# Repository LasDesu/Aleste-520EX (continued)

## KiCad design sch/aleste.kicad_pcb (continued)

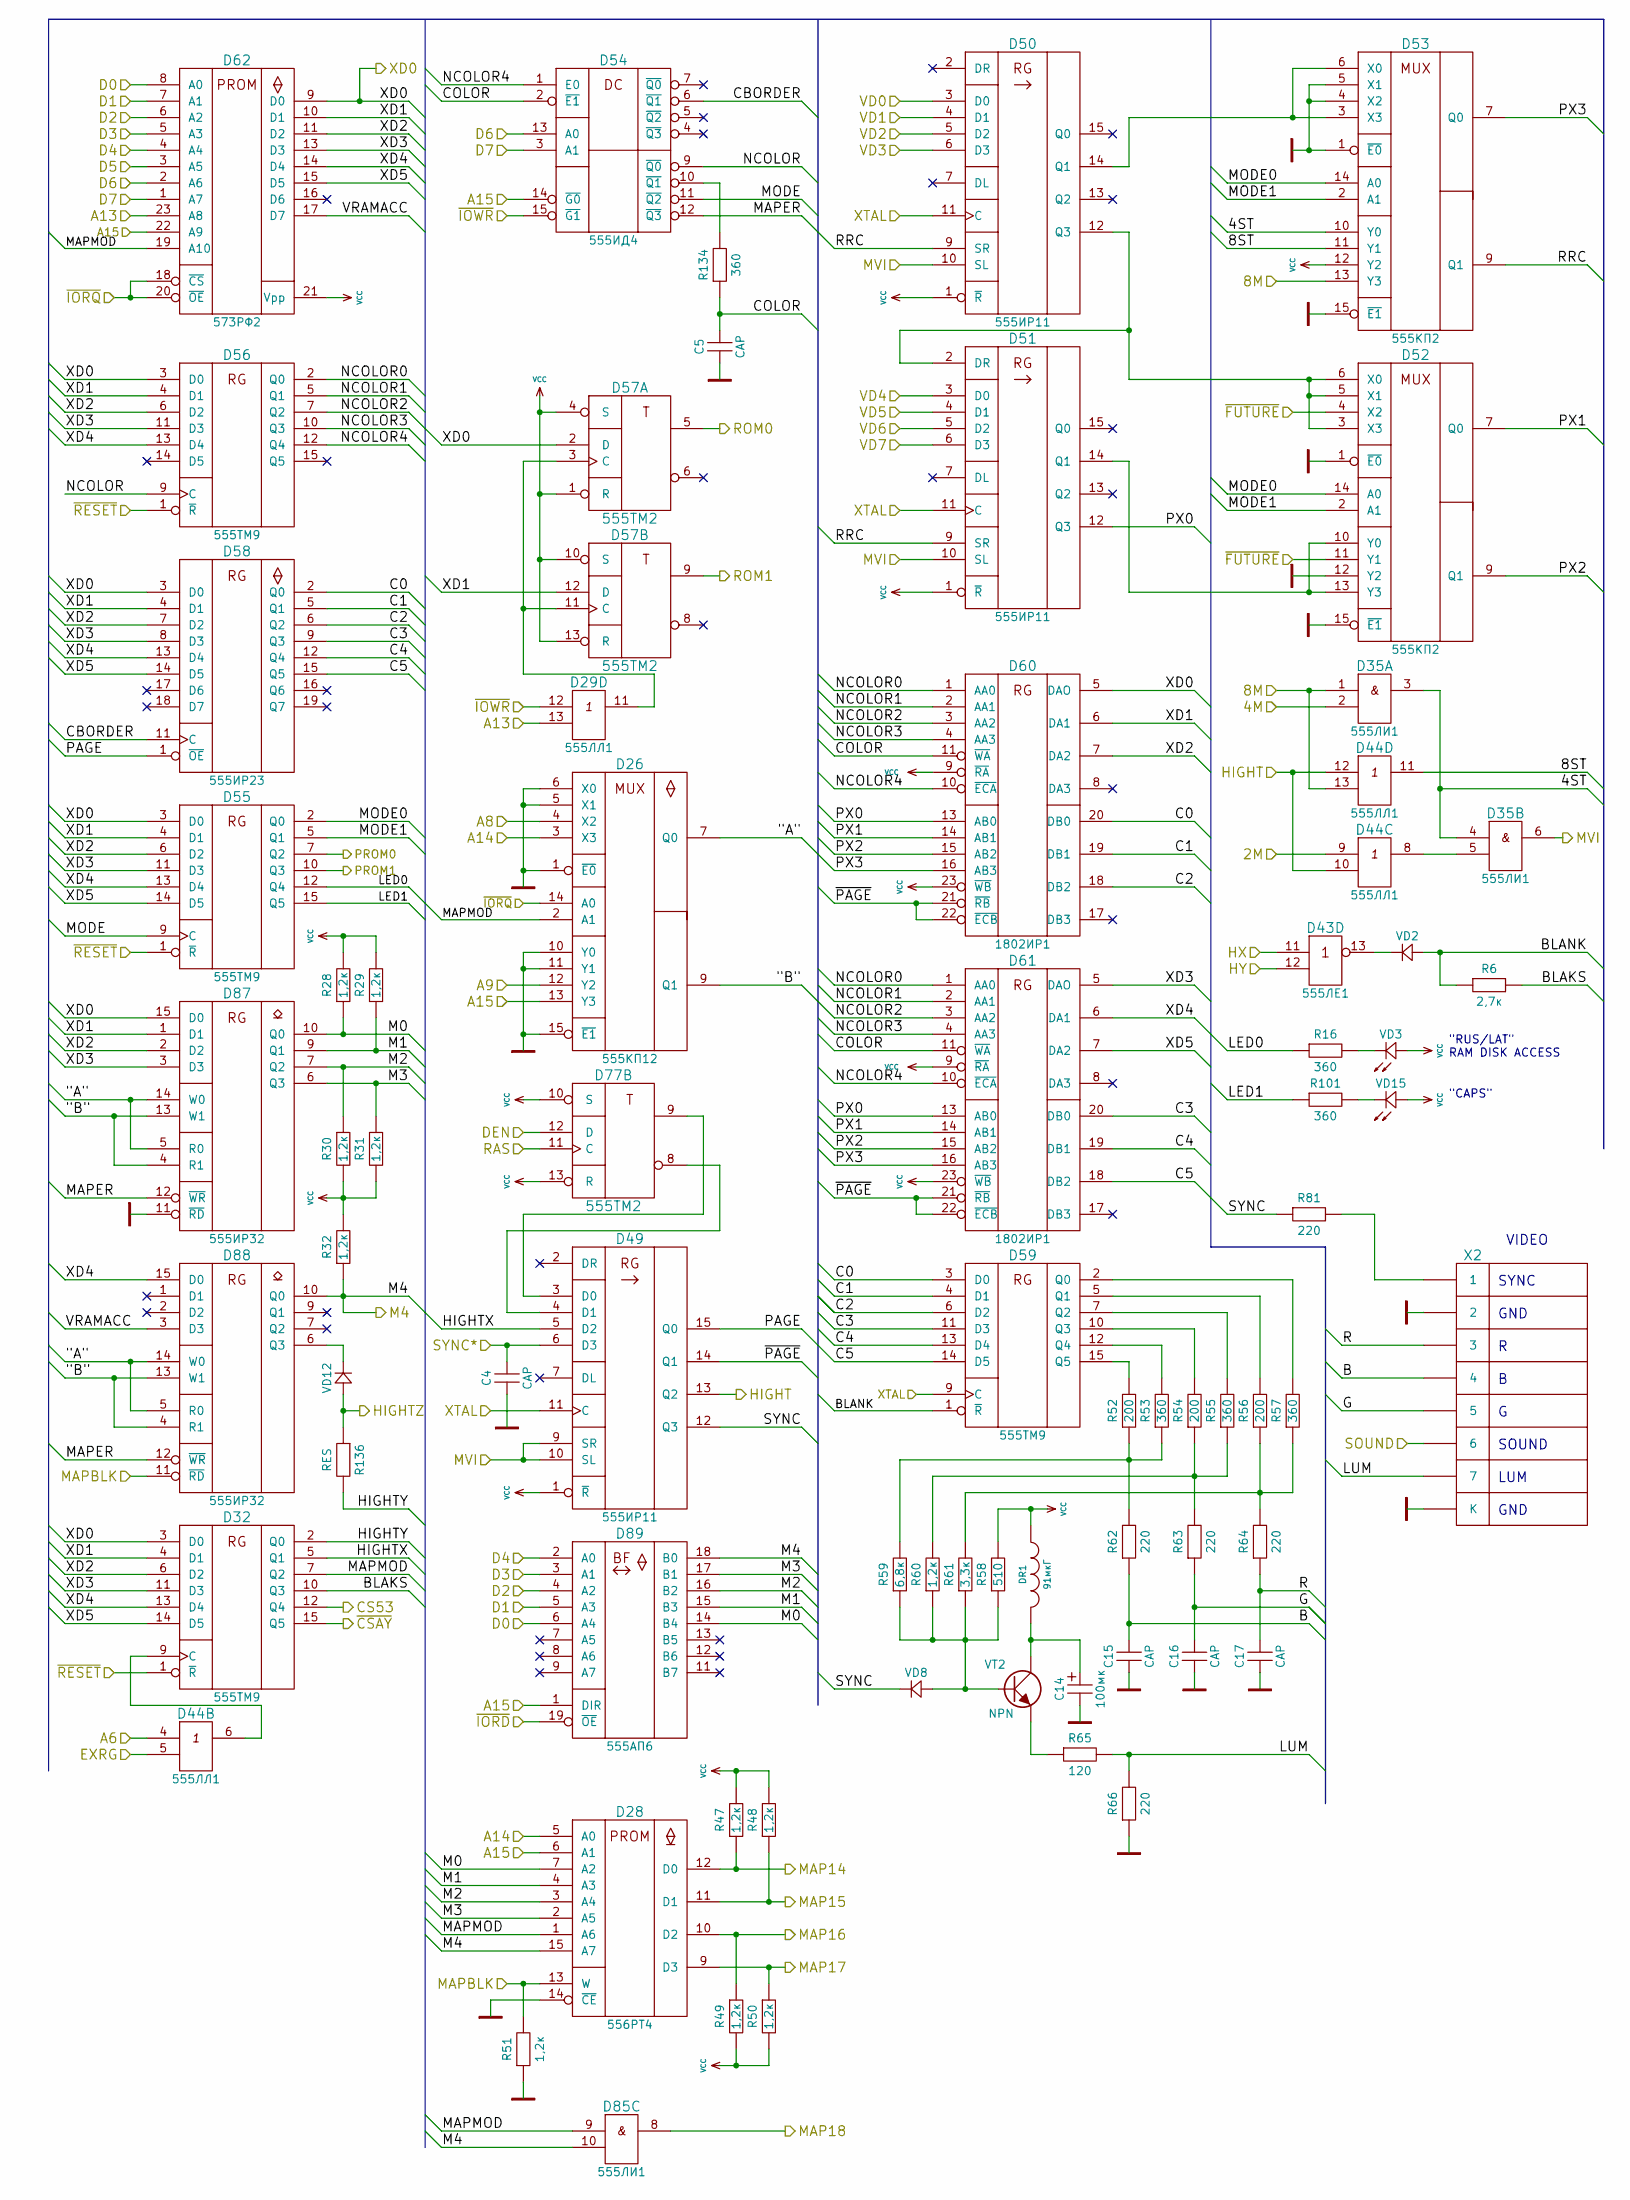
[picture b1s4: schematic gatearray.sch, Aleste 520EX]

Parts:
C4, C5, C15, C16, C17: CAP; C_Disc_D7.5_P2.5
C14: 100мк; C_Radial_D5_L6_P2.5
D26: 555КП12; DIP-16
D28: 556РТ4; DIP-16
D29, D44: 555ЛЛ1; DIP-14
D32, D55, D56, D59: 555ТМ9; DIP-16
D35, D85: 555ЛИ1; DIP-14
D43: 555ЛЕ1; DIP-14
D49, D50, D51: 555ИР11; DIP-16
D52, D53: 555КП2; DIP-16
D54: 555ИД4; DIP-16
D57, D77: 555ТМ2; DIP-14
D58: 555ИР23; DIP-20
D60, D61: 1802ИР1; DIP-24
D62: 573РФ2; DIP-24
D87, D88: 555ИР32; DIP-16
D89: 555АП6; DIP-20
DR1: 91мкГ; Choke_Horizontal_RM15mm
R6: 2,7к; Resistor_Horizontal_RM7.5mm
R16, R53, R55, R57, R101, R134: 360; Resistor_Horizontal_RM7.5mm
R28, R29, R30, R31, R32, R47, R48, R49, R50: 1,2к; Resistor_Vertical_RM2.5mm
R51, R60: 1,2к; Resistor_Horizontal_RM7.5mm
R52, R54, R56: 200; Resistor_Horizontal_RM7.5mm
R58: 510; Resistor_Horizontal_RM7.5mm
R59: 6,8к; Resistor_Horizontal_RM7.5mm
R61: 3,3к; Resistor_Horizontal_RM7.5mm
R62, R63, R64, R66, R81: 220; Resistor_Horizontal_RM7.5mm
R65: 120; Resistor_Horizontal_RM7.5mm
R136: RES; Resistor_Horizontal_RM7.5mm
VD2, VD8, VD12: DIODE_MY; Diode_DO-35_SOD27_Horizontal_RM7.5
VD3, VD15: LED_MY; Pin_Header_Straight_1x02
VT2: NPN; KT315_KT361
X2: CONN-7S; DNR-8F1R

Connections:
/2M: D44.9 (in1); also elsewhere on the board
/4M: D35.2 (in2); also elsewhere on the board
/8M: D35.1 (in1), D44.13 (in2), D53.13 (Y3); also elsewhere on the board
/A6: D44.4 (in1); also elsewhere on the board
/A8: D26.4 (X2); also elsewhere on the board
/A9: D26.12 (Y2); also elsewhere on the board
/A13: D29.13 (in2), D62.23 (A8); also elsewhere on the board
/A14: D26.3 (X3), D28.5 (A0); also elsewhere on the board
/A15: D26.13 (Y3), D28.6 (A1), D54.14 (~G0), D62.22 (A9), D89.1 (DIR); also elsewhere on the board
/CS53: D32.12 (Q4); also elsewhere on the board
/D0: D62.8 (A0), D89.6 (A4); also elsewhere on the board
/D1: D62.7 (A1), D89.5 (A3); also elsewhere on the board
/D2: D62.6 (A2), D89.4 (A2); also elsewhere on the board
/D3: D62.5 (A3), D89.3 (A1); also elsewhere on the board
/D4: D62.4 (A4), D89.2 (A0); also elsewhere on the board
/D5: D62.3 (A5); also elsewhere on the board
/D6: D54.13 (A0), D62.2 (A6); also elsewhere on the board
/D7: D54.3 (A1), D62.1 (A7); also elsewhere on the board
/DEN: D77.12 (D); also elsewhere on the board
/EXRG: D44.5 (in2); also elsewhere on the board
/Gate Array/4ST: D35.3 (out), D35.4 (in1), D53.10 (Y0)
/Gate Array/8ST: D44.11 (out), D53.11 (Y1)
/Gate Array/"A": D26.7 (Q0), D87.5 (R0), D87.14 (W0), D88.5 (R0), D88.14 (W0)
/Gate Array/"B": D26.9 (Q1), D87.4 (R1), D87.13 (W1), D88.4 (R1), D88.13 (W1)
/Gate Array/B: C15.1, R62.1, X2.4
/Gate Array/BLAKS: D32.10 (Q3), R6.2
/Gate Array/BLANK: D59.1 (~R), R6.1, VD2.2
/Gate Array/C0: D58.2 (Q0), D59.3 (D0), D60.20 (DB0)
/Gate Array/C1: D58.5 (Q1), D59.4 (D1), D60.19 (DB1)
/Gate Array/C2: D58.6 (Q2), D59.6 (D2), D60.18 (DB2)
/Gate Array/C3: D58.9 (Q3), D59.11 (D3), D61.20 (DB0)
/Gate Array/C4: D58.12 (Q4), D59.13 (D4), D61.19 (DB1)
/Gate Array/C5: D58.15 (Q5), D59.14 (D5), D61.18 (DB2)
/Gate Array/CBORDER: D54.6 (~Q1), D58.11 (C)
/Gate Array/COLOR: C5.2, D54.2 (~E1), D60.11 (~WA), D61.11 (~WA), R134.1
/Gate Array/G: C16.1, R63.1, X2.5
/Gate Array/HIGHTX: D32.5 (Q1), D49.5 (D2)
/Gate Array/HIGHTY: D32.2 (Q0), R136.2
/Gate Array/LED0: D55.12 (Q4), R16.1
/Gate Array/LED1: D55.15 (Q5), R101.1
/Gate Array/LUM: R65.2, R66.2, X2.7
/Gate Array/M0: D28.7 (A2), D87.10 (Q0), D89.14 (B4), R28.1
/Gate Array/M1: D28.4 (A3), D87.9 (Q1), D89.15 (B3), R29.1
/Gate Array/M2: D28.3 (A4), D87.7 (Q2), D89.16 (B2), R30.1
/Gate Array/M3: D28.2 (A5), D87.6 (Q3), D89.17 (B1), R31.1
/Gate Array/MAPER: D54.12 (~Q3), D87.12 (~WR), D88.12 (~WR)
/Gate Array/MAPMOD: D26.2 (A1), D28.1 (A6), D32.7 (Q2), D62.19 (A10), D85.9 (in1)
/Gate Array/MODE: D54.11 (~Q2), D55.9 (C)
/Gate Array/MODE0: D52.14 (A0), D53.14 (A0), D55.2 (Q0)
/Gate Array/MODE1: D52.2 (A1), D53.2 (A1), D55.5 (Q1)
/Gate Array/NCOLOR: D54.9 (~Q0), D56.9 (C)
/Gate Array/NCOLOR0: D56.2 (Q0), D60.1 (AA0), D61.1 (AA0)
/Gate Array/NCOLOR1: D56.5 (Q1), D60.2 (AA1), D61.2 (AA1)
/Gate Array/NCOLOR2: D56.7 (Q2), D60.3 (AA2), D61.3 (AA2)
/Gate Array/NCOLOR3: D56.10 (Q3), D60.4 (AA3), D61.4 (AA3)
/Gate Array/NCOLOR4: D54.1 (E0), D56.12 (Q4), D60.10 (~ECA), D61.10 (~ECA)
/Gate Array/PAGE: D49.15 (Q0), D58.1 (~OE)
/Gate Array/PX0: D51.12 (Q3), D60.13 (AB0), D61.13 (AB0)
/Gate Array/PX1: D52.7 (Q0), D60.14 (AB1), D61.14 (AB1)
/Gate Array/PX2: D52.9 (Q1), D60.15 (AB2), D61.15 (AB2)
/Gate Array/PX3: D53.7 (Q0), D60.16 (AB3), D61.16 (AB3)
/Gate Array/R: C17.1, R64.1, X2.3
/Gate Array/RRC: D50.9 (SR), D51.9 (SR), D53.9 (Q1)
/Gate Array/SYNC: D49.12 (Q3), R81.1, VD8.1
/Gate Array/VRAMACC: D62.17 (D7), D88.3 (D3)
/Gate Array/XD1: D32.4 (D1), D55.4 (D1), D56.4 (D1), D57.12 (D), D58.4 (D1), D60.6 (DA1), D62.10 (D1), D87.1 (D1)
/Gate Array/XD2: D32.6 (D2), D55.6 (D2), D56.6 (D2), D58.7 (D2), D60.7 (DA2), D62.11 (D2), D87.2 (D2)
/Gate Array/XD3: D32.11 (D3), D55.11 (D3), D56.11 (D3), D58.8 (D3), D61.5 (DAO), D62.13 (D3), D87.3 (D3)
/Gate Array/XD4: D32.13 (D4), D55.13 (D4), D56.13 (D4), D58.13 (D4), D61.6 (DA1), D62.14 (D4), D88.15 (D0)
/Gate Array/XD5: D32.14 (D5), D55.14 (D5), D58.14 (D5), D61.7 (DA2), D62.15 (D5)
/Gate Array/~PAGE: D49.14 (Q1), D60.21 (~RB), D60.22 (~ECB), D61.21 (~RB), D61.22 (~ECB)
/HIGHT: D44.10 (in2), D44.12 (in1), D49.13 (Q2); also elsewhere on the board
/HIGHTZ: R136.1, VD12.2; also elsewhere on the board
/HX: D43.11 (in1); also elsewhere on the board
/HY: D43.12 (in2); also elsewhere on the board
/M4: D28.15 (A7), D85.10 (in2), D88.10 (Q0), D89.18 (B0), R32.1; also elsewhere on the board
/MAP14: D28.12 (D0), R47.1; also elsewhere on the board
/MAP15: D28.11 (D1), R48.1; also elsewhere on the board
/MAP16: D28.10 (D2), R49.1; also elsewhere on the board
/MAP17: D28.9 (D3), R50.1; also elsewhere on the board
/MAP18: D85.8 (out); also elsewhere on the board
/MAPBLK: D28.13 (W), D88.11 (~RD), R51.2; also elsewhere on the board
/MVI: D35.6 (out), D49.9 (SR), D49.10 (SL), D50.10 (SL), D51.10 (SL); also elsewhere on the board
/PROM0: D55.7 (Q2); also elsewhere on the board
/PROM1: D55.10 (Q3); also elsewhere on the board
/RAS: D77.11 (C); also elsewhere on the board
/ROM0: D57.5; also elsewhere on the board
/ROM1: D57.9; also elsewhere on the board
/SOUND: X2.6; also elsewhere on the board
/SYNC*: C4.2, D49.6 (D3); also elsewhere on the board
/VD0: D50.3 (D0); also elsewhere on the board
/VD1: D50.4 (D1); also elsewhere on the board
/VD2: D50.5 (D2); also elsewhere on the board
/VD3: D50.6 (D3); also elsewhere on the board
/VD4: D51.3 (D0); also elsewhere on the board
/VD5: D51.4 (D1); also elsewhere on the board
/VD6: D51.5 (D2); also elsewhere on the board
/VD7: D51.6 (D3); also elsewhere on the board
/XD0: D32.3 (D0), D55.3 (D0), D56.3 (D0), D57.2 (D), D58.3 (D0), D60.5 (DAO), D62.9 (D0), D87.15 (D0); also elsewhere on the board
/XTAL: D49.11 (C), D50.11 (C), D51.11 (C), D59.9 (C); also elsewhere on the board
/~CSAY: D32.15 (Q5); also elsewhere on the board
/~FUTURE: D52.4 (X2), D52.11 (Y1); also elsewhere on the board
/~IORD: D89.19 (~OE); also elsewhere on the board
/~IORQ: D26.14 (A0), D62.18 (~CS), D62.20 (~OE); also elsewhere on the board
/~IOWR: D29.12 (in1), D54.15 (~G1); also elsewhere on the board
/~RESET: D32.1 (~R), D55.1 (~R), D56.1 (~R); also elsewhere on the board
GND: C4.1, C5.1, C14.2, C15.2, C16.2, C17.2, D26.1 (~E0), D26.5 (X1), D26.6 (X0), D26.8 (GND), D26.10 (Y0), D26.11 (Y1), D26.15 (~E1), D28.8 (GND), D28.14 (~CE), D29.7 (GND), D32.8 (GND), D35.7 (GND), D43.7 (GND), D44.7 (GND), D49.8 (GND), D50.8 (GND), D51.8 (GND), D52.1 (~E0), D52.8 (GND), D52.12 (Y2), D52.15 (~E1), D53.1 (~E0), D53.4 (X2), D53.5 (X1), D53.8 (GND), D53.15 (~E1), D54.8 (GND), D55.8 (GND), D56.8 (GND), D57.7 (GND), D58.10 (GND), D59.8 (GND), D60.12 (GND), D61.12 (GND), D62.12 (GND), D77.7 (GND), D85.7 (GND), D87.8 (GND), D87.11 (~RD), D88.8 (GND), D89.10 (GND), R51.1, R66.1, X2.2, X2.S (К); also elsewhere on the board
unnamed: C14.1, DR1.2, VT2.C
unnamed: D29.11 (out), D57.3 (C), D57.11 (C)
unnamed: D32.9 (C), D44.6 (out)
unnamed: D35.5 (in2), D44.8 (out)
unnamed: D43.13 (out), VD2.1
unnamed: D49.3 (D0), D77.9
unnamed: D49.4 (D1), D77.8
unnamed: D50.12 (Q3), D51.2 (DR), D52.3 (X3), D52.5 (X1), D52.6 (X0)
unnamed: D50.14 (Q1), D53.3 (X3), D53.6 (X0)
unnamed: D51.14 (Q1), D52.10 (Y0), D52.13 (Y3)
unnamed: D54.10 (~Q1), R134.2
unnamed: D59.2 (Q0), R57.2
unnamed: D59.5 (Q1), R56.2
unnamed: D59.7 (Q2), R55.2
unnamed: D59.10 (Q3), R54.2
unnamed: D59.12 (Q4), R53.2
unnamed: D59.15 (Q5), R52.2
unnamed: D88.6 (Q3), VD12.1
unnamed: R16.2, VD3.1
unnamed: R52.1, R53.1, R59.2, R62.2
unnamed: R54.1, R55.1, R60.2, R63.2
unnamed: R56.1, R57.1, R61.2, R64.2
unnamed: R58.1, R59.1, R60.1, R61.1, VD8.2, VT2.B
unnamed: R65.1, VT2.E
unnamed: R81.2, X2.1
unnamed: R101.2, VD15.1
VCC: D26.16 (VCC), D28.16 (VCC), D29.14 (VCC), D32.16 (VCC), D35.14 (VCC), D43.14 (VCC), D44.14 (VCC), D49.1 (~R), D49.16 (VCC), D50.1 (~R), D50.16 (VCC), D51.1 (~R), D51.16 (VCC), D52.16 (VCC), D53.12 (Y2), D53.16 (VCC), D54.16 (VCC), D55.16 (VCC), D56.16 (VCC), D57.1 (R), D57.4 (S), D57.10 (S), D57.13 (R), D57.14 (VCC), D58.20 (VCC), D59.16 (VCC), D60.9 (~RA), D60.23 (~WB), D60.24 (VCC), D61.9 (~RA), D61.23 (~WB), D61.24 (VCC), D62.21 (Vpp), D62.24 (VCC), D77.10 (S), D77.13 (R), D77.14 (VCC), D85.14 (VCC), D87.16 (VCC), D88.16 (VCC), D89.20 (VCC), DR1.1, R28.2, R29.2, R30.2, R31.2, R32.2, R47.2, R48.2, R49.2, R50.2, R58.2, VD3.2, VD15.2; also elsewhere on the board

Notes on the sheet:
"RUS/LAT" RAM DISK ACCESS
"CAPS"
VIDEO
SYNC
GND
LUM
SOUND

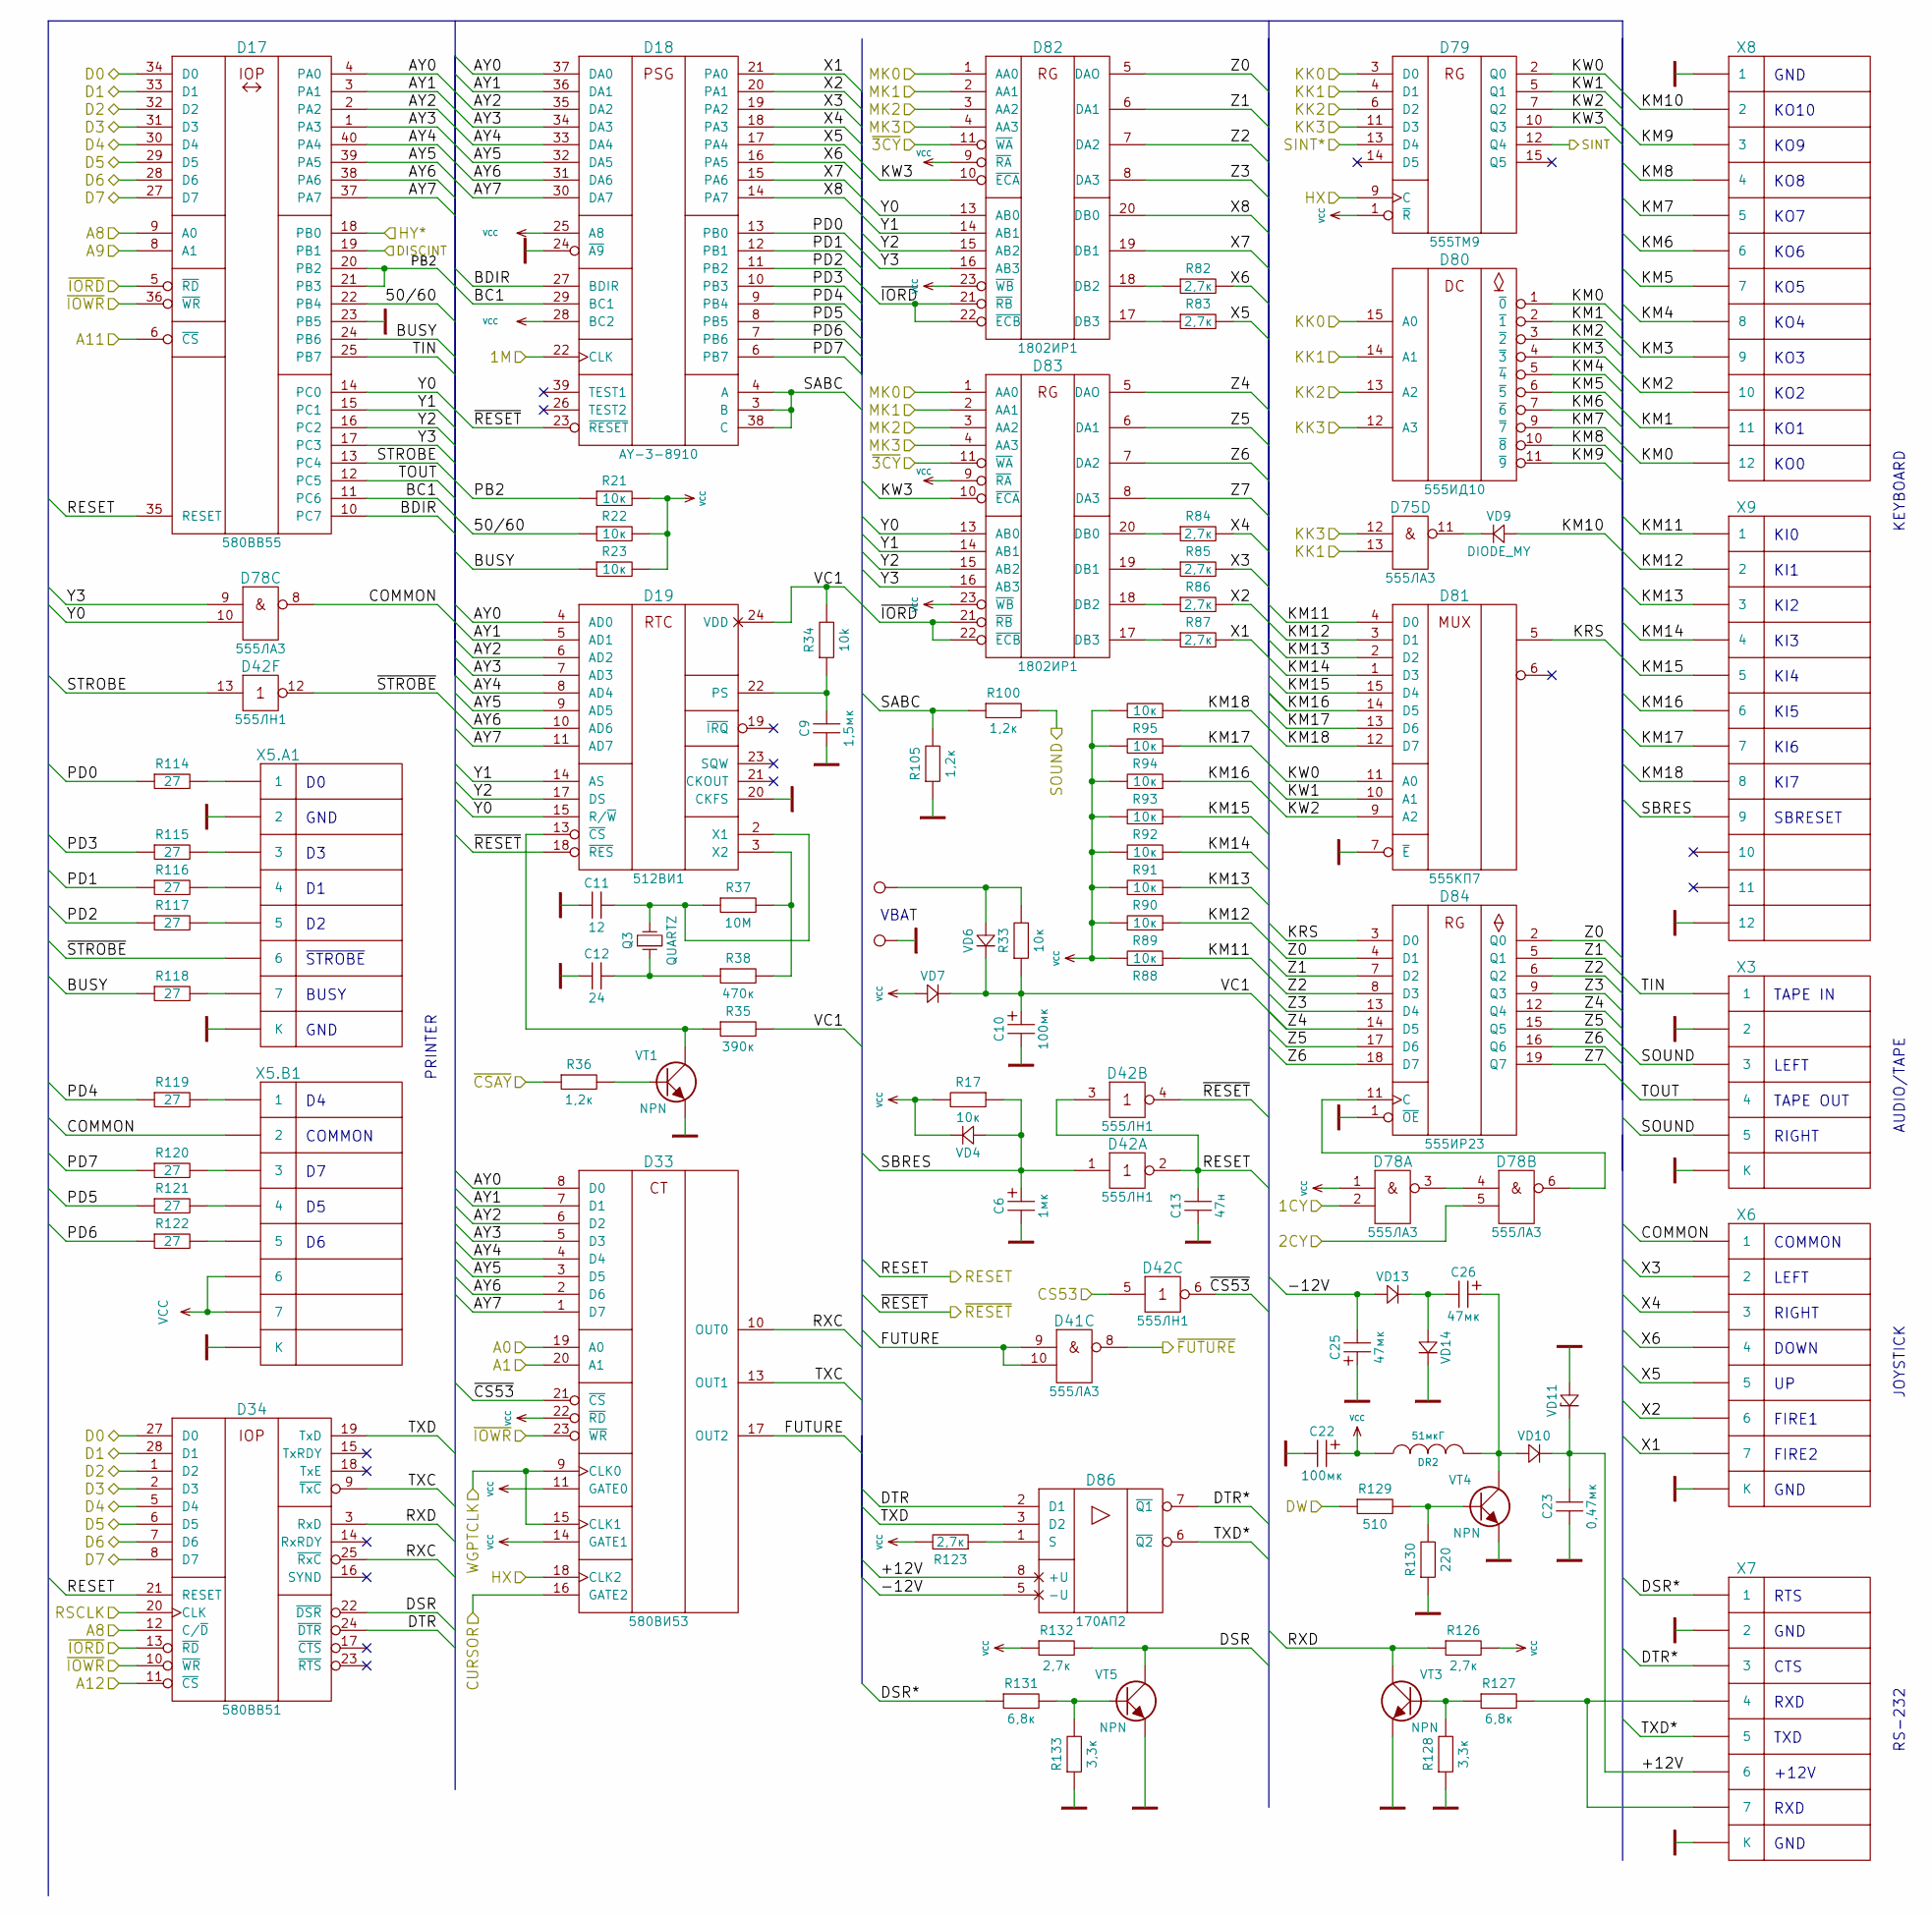
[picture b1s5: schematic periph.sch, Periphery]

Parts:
C6: 1мк; C_Radial_D5_L6_P2.5
C9: 1,5мк; C_Disc_D7.5_P2.5
C10, C22: 100мк; C_Radial_D5_L6_P2.5
C11: 12; C_Disc_D7.5_P2.5
C12: 24; C_Disc_D7.5_P2.5
C13: 47н; C_Disc_D7.5_P2.5
C23: 0,47мк; C_Disc_D7.5_P2.5
C25, C26: 47мк; C_Radial_D5_L6_P2.5
D17: 580ВВ55; DIP-40
D18: AY-3-8910; DIP-40
D19: 512ВИ1; DIP-24
D33: 580ВИ53; DIP-24
D34: 580ВВ51; DIP-28
D41, D75, D78: 555ЛА3; DIP-14
D42: 555ЛН1; DIP-14
D79: 555ТМ9; DIP-16
D80: 555ИД10; DIP-16
D81: 555КП7; DIP-16
D82, D83: 1802ИР1; DIP-24
D84: 555ИР23; DIP-20
D86: 170АП2; DIP-8
DR2: 51мкГ; Choke_Horizontal_RM15mm
P7, P8: PIN
Q3: QUARTZ; Crystal_Round_Vertical_5mm
R17, R21, R22, R23, R88, R89, R90, R91, R92, R93, R94, R95: 10к; Resistor_Vertical_RM2.5mm
R33: 10к; Resistor_Horizontal_RM7.5mm
R34: 10k; Resistor_Horizontal_RM7.5mm
R35: 390к; Resistor_Horizontal_RM7.5mm
R36, R100, R105: 1,2к; Resistor_Horizontal_RM7.5mm
R37: 10М; Resistor_Horizontal_RM7.5mm
R38: 470к; Resistor_Horizontal_RM7.5mm
R82, R83, R84, R85, R86, R87, R123, R126, R132: 2,7к; Resistor_Horizontal_RM7.5mm
R114, R115, R116, R117, R118, R119, R120, R121, R122: 27; Resistor_Horizontal_RM7.5mm
R127, R131: 6,8к; Resistor_Horizontal_RM7.5mm
R128, R133: 3,3к; Resistor_Horizontal_RM7.5mm
R129: 510; Resistor_Horizontal_RM7.5mm
R130: 220; Resistor_Horizontal_RM7.5mm
VD4, VD6, VD7, VD9, VD10, VD13, VD14: DIODE_MY; Diode_DO-35_SOD27_Horizontal_RM7.5
VD11: ZDIODE_MY; Diode_DO-35_SOD27_Horizontal_RM7.5
VT1, VT3, VT4, VT5: NPN; KT315_KT361
X3: CONN-5S; DNR-5F1R
X5.A1, X5.B1, X6, X7: CONN-7S; DNR-8F1R
X8, X9: CONN-12; FB-12

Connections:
/1CY: D78.2 (in2); also elsewhere on the board
/1M: D18.22 (CLK); also elsewhere on the board
/2CY: D78.5 (in2); also elsewhere on the board
/A0: D33.19 (A0); also elsewhere on the board
/A1: D33.20 (A1); also elsewhere on the board
/A8: D17.9 (A0), D34.12 (C/~D); also elsewhere on the board
/A9: D17.8 (A1); also elsewhere on the board
/A11: D17.6 (~CS); also elsewhere on the board
/A12: D34.11 (~CS); also elsewhere on the board
/CS53: D42.5 (in); also elsewhere on the board
/CURSOR: D33.16 (GATE2); also elsewhere on the board
/D0: D17.34 (D0), D34.27 (D0); also elsewhere on the board
/D1: D17.33 (D1), D34.28 (D1); also elsewhere on the board
/D2: D17.32 (D2), D34.1 (D2); also elsewhere on the board
/D3: D17.31 (D3), D34.2 (D3); also elsewhere on the board
/D4: D17.30 (D4), D34.5 (D4); also elsewhere on the board
/D5: D17.29 (D5), D34.6 (D5); also elsewhere on the board
/D6: D17.28 (D6), D34.7 (D6); also elsewhere on the board
/D7: D17.27 (D7), D34.8 (D7); also elsewhere on the board
/DISCINT: D17.19 (PB1); also elsewhere on the board
/DW: R129.1; also elsewhere on the board
/HX: D33.18 (CLK2), D79.9 (C); also elsewhere on the board
/HY*: D17.18 (PB0); also elsewhere on the board
/KK0: D79.3 (D0), D80.15 (A0); also elsewhere on the board
/KK1: D75.13 (in2), D79.4 (D1), D80.14 (A1); also elsewhere on the board
/KK2: D79.6 (D2), D80.13 (A2); also elsewhere on the board
/KK3: D75.12 (in1), D79.11 (D3), D80.12 (A3); also elsewhere on the board
/MK0: D82.1 (AA0), D83.1 (AA0); also elsewhere on the board
/MK1: D82.2 (AA1), D83.2 (AA1); also elsewhere on the board
/MK2: D82.3 (AA2), D83.3 (AA2); also elsewhere on the board
/MK3: D82.4 (AA3), D83.4 (AA3); also elsewhere on the board
/Periphery/50/60: D17.22 (PB4), R22.1
/Periphery/+12V: C23.2, D86.8 (+U), VD10.1, VD11.1, X7.6
/Periphery/-12V: C25.2, D86.5 (-U), VD13.2
/Periphery/AY0: D17.4 (PA0), D18.37 (DA0), D19.4 (AD0), D33.8 (D0)
/Periphery/AY1: D17.3 (PA1), D18.36 (DA1), D19.5 (AD1), D33.7 (D1)
/Periphery/AY2: D17.2 (PA2), D18.35 (DA2), D19.6 (AD2), D33.6 (D2)
/Periphery/AY3: D17.1 (PA3), D18.34 (DA3), D19.7 (AD3), D33.5 (D3)
/Periphery/AY4: D17.40 (PA4), D18.33 (DA4), D19.8 (AD4), D33.4 (D4)
/Periphery/AY5: D17.39 (PA5), D18.32 (DA5), D19.9 (AD5), D33.3 (D5)
/Periphery/AY6: D17.38 (PA6), D18.31 (DA6), D19.10 (AD6), D33.2 (D6)
/Periphery/AY7: D17.37 (PA7), D18.30 (DA7), D19.11 (AD7), D33.1 (D7)
/Periphery/BC1: D17.11 (PC6), D18.29 (BC1)
/Periphery/BDIR: D17.10 (PC7), D18.27 (BDIR)
/Periphery/BUSY: D17.24 (PB6), R23.1, R118.1
/Periphery/COMMON: D78.8 (out), X5.B1.2, X6.1
/Periphery/DSR: D34.22 (~DSR), R132.2, VT5.C
/Periphery/DSR*: R131.1, X7.1
/Periphery/DTR: D34.24 (~DTR), D86.2 (D1)
/Periphery/DTR*: D86.7 (~Q1), X7.3
/Periphery/FUTURE: D33.17 (OUT2), D41.9 (in1), D41.10 (in2)
/Periphery/KM0: D80.1 (~0), X8.12
/Periphery/KM1: D80.2 (~1), X8.11
/Periphery/KM2: D80.3 (~2), X8.10
/Periphery/KM3: D80.4 (~3), X8.9
/Periphery/KM4: D80.5 (~4), X8.8
/Periphery/KM5: D80.6 (~5), X8.7
/Periphery/KM6: D80.7 (~6), X8.6
/Periphery/KM7: D80.9 (~7), X8.5
/Periphery/KM8: D80.10 (~8), X8.4
/Periphery/KM9: D80.11 (~9), X8.3
/Periphery/KM10: VD9.2, X8.2
/Periphery/KM11: D81.4 (D0), R88.1, X9.1
/Periphery/KM12: D81.3 (D1), R89.1, X9.2
/Periphery/KM13: D81.2 (D2), R90.1, X9.3
/Periphery/KM14: D81.1 (D3), R91.1, X9.4
/Periphery/KM15: D81.15 (D4), R92.1, X9.5
/Periphery/KM16: D81.14 (D5), R93.1, X9.6
/Periphery/KM17: D81.13 (D6), R94.1, X9.7
/Periphery/KM18: D81.12 (D7), R95.1, X9.8
/Periphery/KRS: D81.5, D84.3 (D0)
/Periphery/KW0: D79.2 (Q0), D81.11 (A0)
/Periphery/KW1: D79.5 (Q1), D81.10 (A1)
/Periphery/KW2: D79.7 (Q2), D81.9 (A2)
/Periphery/KW3: D79.10 (Q3), D82.10 (~ECA), D83.10 (~ECA)
/Periphery/PB2: D17.20 (PB2), D17.21 (PB3), R21.1
/Periphery/PD0: D18.13 (PB0), R114.1
/Periphery/PD1: D18.12 (PB1), R116.1
/Periphery/PD2: D18.11 (PB2), R117.1
/Periphery/PD3: D18.10 (PB3), R115.1
/Periphery/PD4: D18.9 (PB4), R119.1
/Periphery/PD5: D18.8 (PB5), R121.1
/Periphery/PD6: D18.7 (PB6), R122.1
/Periphery/PD7: D18.6 (PB7), R120.1
/Periphery/RXC: D33.10 (OUT0), D34.25 (~RxC)
/Periphery/RXD: D34.3 (RxD), R126.1, VT3.C
/Periphery/SABC: D18.3 (B), D18.4 (A), D18.38 (C), R100.1, R105.2
/Periphery/SBRES: C6.1, D42.1 (in), R17.1, VD4.2, X9.9
/Periphery/STROBE: D17.13 (PC4), D42.13 (in)
/Periphery/TIN: D17.25 (PB7), X3.1
/Periphery/TOUT: D17.12 (PC5), X3.4
/Periphery/TXC: D33.13 (OUT1), D34.9 (~TxC)
/Periphery/TXD: D34.19 (TxD), D86.3 (D2)
/Periphery/TXD*: D86.6 (~Q2), X7.5
/Periphery/VC1: C10.1, D19.24 (VDD), R33.1, R34.2, R35.2, VD6.1, VD7.1
/Periphery/X1: D18.21 (PA0), R87.2, X6.7
/Periphery/X2: D18.20 (PA1), R86.2, X6.6
/Periphery/X3: D18.19 (PA2), R85.2, X6.2
/Periphery/X4: D18.18 (PA3), R84.2, X6.3
/Periphery/X5: D18.17 (PA4), R83.2, X6.5
/Periphery/X6: D18.16 (PA5), R82.2, X6.4
/Periphery/X7: D18.15 (PA6), D82.19 (DB1)
/Periphery/X8: D18.14 (PA7), D82.20 (DB0)
/Periphery/Y0: D17.14 (PC0), D19.15 (R/~W), D78.10 (in2), D82.13 (AB0), D83.13 (AB0)
/Periphery/Y1: D17.15 (PC1), D19.14 (AS), D82.14 (AB1), D83.14 (AB1)
/Periphery/Y2: D17.16 (PC2), D19.17 (DS), D82.15 (AB2), D83.15 (AB2)
/Periphery/Y3: D17.17 (PC3), D78.9 (in1), D82.16 (AB3), D83.16 (AB3)
/Periphery/Z0: D82.5 (DAO), D84.2 (Q0), D84.4 (D1)
/Periphery/Z1: D82.6 (DA1), D84.5 (Q1), D84.7 (D2)
/Periphery/Z2: D82.7 (DA2), D84.6 (Q2), D84.8 (D3)
/Periphery/Z3: D82.8 (DA3), D84.9 (Q3), D84.13 (D4)
/Periphery/Z4: D83.5 (DAO), D84.12 (Q4), D84.14 (D5)
/Periphery/Z5: D83.6 (DA1), D84.15 (Q5), D84.17 (D6)
/Periphery/Z6: D83.7 (DA2), D84.16 (Q6), D84.18 (D7)
/Periphery/Z7: D83.8 (DA3), D84.19 (Q7)
/Periphery/~CS53: D33.21 (~CS), D42.6 (out)
/Periphery/~STROBE: D42.12 (out), X5.A1.6
/RESET: C13.2, D17.35 (RESET), D34.21 (RESET), D42.2 (out), D42.3 (in); also elsewhere on the board
/RSCLK: D34.20 (CLK); also elsewhere on the board
/SINT: D79.12 (Q4); also elsewhere on the board
/SINT*: D79.13 (D4); also elsewhere on the board
/SOUND: R100.2, X3.3, X3.5; also elsewhere on the board
/WGPTCLK: D33.9 (CLK0), D33.15 (CLK1); also elsewhere on the board
/~3CY: D82.11 (~WA), D83.11 (~WA); also elsewhere on the board
/~CSAY: R36.1; also elsewhere on the board
/~FUTURE: D41.8 (out); also elsewhere on the board
/~IORD: D17.5 (~RD), D34.13 (~RD), D82.21 (~RB), D82.22 (~ECB), D83.21 (~RB), D83.22 (~ECB); also elsewhere on the board
/~IOWR: D17.36 (~WR), D33.23 (~WR), D34.10 (~WR); also elsewhere on the board
/~RESET: D18.23 (~RESET), D19.18 (~RES), D42.4 (out); also elsewhere on the board
GND: C6.2, C9.1, C10.2, C11.1, C12.1, C13.1, C22.2, C23.1, C25.1, D17.7 (GND), D17.23 (PB5), D18.1 (GND), D18.24 (~A9), D19.12 (GND), D19.20 (CKFS), D33.12 (GND), D34.4 (GND), D41.7 (GND), D42.7 (GND), D75.7 (GND), D78.7 (GND), D79.8 (GND), D80.8 (GND), D81.7 (~E), D81.8 (GND), D82.12 (GND), D83.12 (GND), D84.1 (~OE), D84.10 (GND), D86.4 (GND), P8.1, R105.1, R128.1, R130.1, R133.1, VD11.2, VD14.1, VT1.E, VT3.E, VT4.E, VT5.E, X3.2, X3.S (К), X5.A1.2, X5.A1.S (К), X5.B1.S (К), X6.S (К), X7.2, X7.S (К), X8.1, X9.12; also elsewhere on the board
unnamed: C9.2, D19.22 (PS), R34.1
unnamed: C11.2, D19.2 (X1), Q3.2, R37.1
unnamed: C12.2, Q3.1, R38.1
unnamed: C26.1, DR2.2, VD10.2, VT4.C
unnamed: C26.2, VD13.1, VD14.2
unnamed: D19.3 (X2), R37.2, R38.2
unnamed: D19.13 (~CS), R35.1, VT1.C
unnamed: D75.11 (out), VD9.1
unnamed: D78.3 (out), D78.4 (in1)
unnamed: D78.6 (out), D84.11 (C)
unnamed: D82.17 (DB3), R83.1
unnamed: D82.18 (DB2), R82.1
unnamed: D83.17 (DB3), R87.1
unnamed: D83.18 (DB2), R86.1
unnamed: D83.19 (DB1), R85.1
unnamed: D83.20 (DB0), R84.1
unnamed: D86.1 (S), R123.1
unnamed 511: P7.1, R33.2, VD6.2; also elsewhere on the board
unnamed: R36.2, VT1.B
unnamed: R114.2, X5.A1.1
unnamed: R115.2, X5.A1.3
unnamed: R116.2, X5.A1.4
unnamed: R117.2, X5.A1.5
unnamed: R118.2, X5.A1.7
unnamed: R119.2, X5.B1.1
unnamed: R120.2, X5.B1.3
unnamed: R121.2, X5.B1.4
unnamed: R122.2, X5.B1.5
unnamed: R127.1, R128.2, VT3.B
unnamed: R127.2, X7.4, X7.7
unnamed: R129.2, R130.2, VT4.B
unnamed: R131.2, R133.2, VT5.B
VCC: C22.1, D17.26 (VCC), D18.25 (A8), D18.28 (BC2), D18.40 (VCC), D33.11 (GATE0), D33.14 (GATE1), D33.22 (~RD), D33.24 (VCC), D34.26 (VCC), D41.14 (VCC), D42.14 (VCC), D75.14 (VCC), D78.1 (in1), D78.14 (VCC), D79.1 (~R), D79.16 (VCC), D80.16 (VCC), D81.16 (VCC), D82.9 (~RA), D82.23 (~WB), D82.24 (VCC), D83.9 (~RA), D83.23 (~WB), D83.24 (VCC), D84.20 (VCC), DR2.1, R17.2, R21.2, R22.2, R23.2, R88.2, R89.2, R90.2, R91.2, R92.2, R93.2, R94.2, R95.2, R123.2, R126.2, R132.1, VD4.1, VD7.2, X5.B1.6, X5.B1.7; also elsewhere on the board

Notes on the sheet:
SBRESET
GND
KO0
KO1
KO2
KO3
KO4
KO5
KO6
KO7
KO8
KO9
KO10
KI0
KI1
KI2
KI3
KI4
KI5
KI6
KI7
TAPE IN
TAPE OUT
LEFT
RIGHT
COMMON
DOWN
FIRE1
FIRE2
GND
~STROBE
BUSY
PRINTER
KEYBOARD
AUDIO/TAPE
JOYSTICK
VBAT
RTS
CTS
RXD
